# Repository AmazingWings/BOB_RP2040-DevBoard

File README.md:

<div align="center">

# BOB
### A Raspberry Pi RP2040 development board

### [Key Features](#key-features) • [PCB](#pcb) • [Credits](#credits) • [License](#license)

</div>

---

## Welcome!
Hi! This is my first SMT board! It is a custom RP2040 development board named BOB. I chose BOB as the name because I like Bob; it's a fun name to say. But on the other hand, it is designed to act as a platform for me to learn SMT board design. The reason why I made it was not only to learn how to make a fully SMT board, but to serve as a platform for learning for my future flight computer designs I will do for my rockets. I wanted to transition away from using software like EasyEDA to more professional software like KiCad, which is much more widely used. Through this project, I not only learned SMT schematic design but also routing. In EasyEDA, I used to autoroute my components, but in KiCad and through this project, I learned how to route components and place components by myself, transitioning away from my dependencies with breakout boards. 

### Key features:
1. Dual-core processor with up to 133 MHz in speed.
2. 264 KB of on-chip SRAM.
3. Programmable through USB-C.
4. 30 GPIO pins that can run I2C, SPI, and UART. 
5. 2-layer PCB design: top layer for components and bottom layer for ground wiring and signal routing, along with the top layer for signal wiring and power wiring.

---

## PCB

### Schematic Design 

### PCB Design

### 3D Design

### JLC PCB 3D Design

### BOM

### Final Cost Estimate

---

## Credits
1. https://macondo.hackclub.com/docs/build-a-devboard
2. [KiCad](https://www.kicad.org/) 
3. [JLCPCB](https://jlcpcb.com/)

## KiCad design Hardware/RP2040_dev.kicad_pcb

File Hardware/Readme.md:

<div align="center">

# Production Files
### RP2040 BOB Devboard
</div>

---

This folder contains all the necessary production files required to manufacture the **RP2040 BOB devboard**. 

---

## 🛠️ How to Use (Manufacturing)

If you want to order this board, simply **drag and drop the entire folder into JLCPCB**. Their system will automatically detect and compile all the necessary files you need for production.

## 📄 Key Files

* **BOM (Bill of Materials):** Provided in standard `.csv` format, ready for component sourcing and assembly.

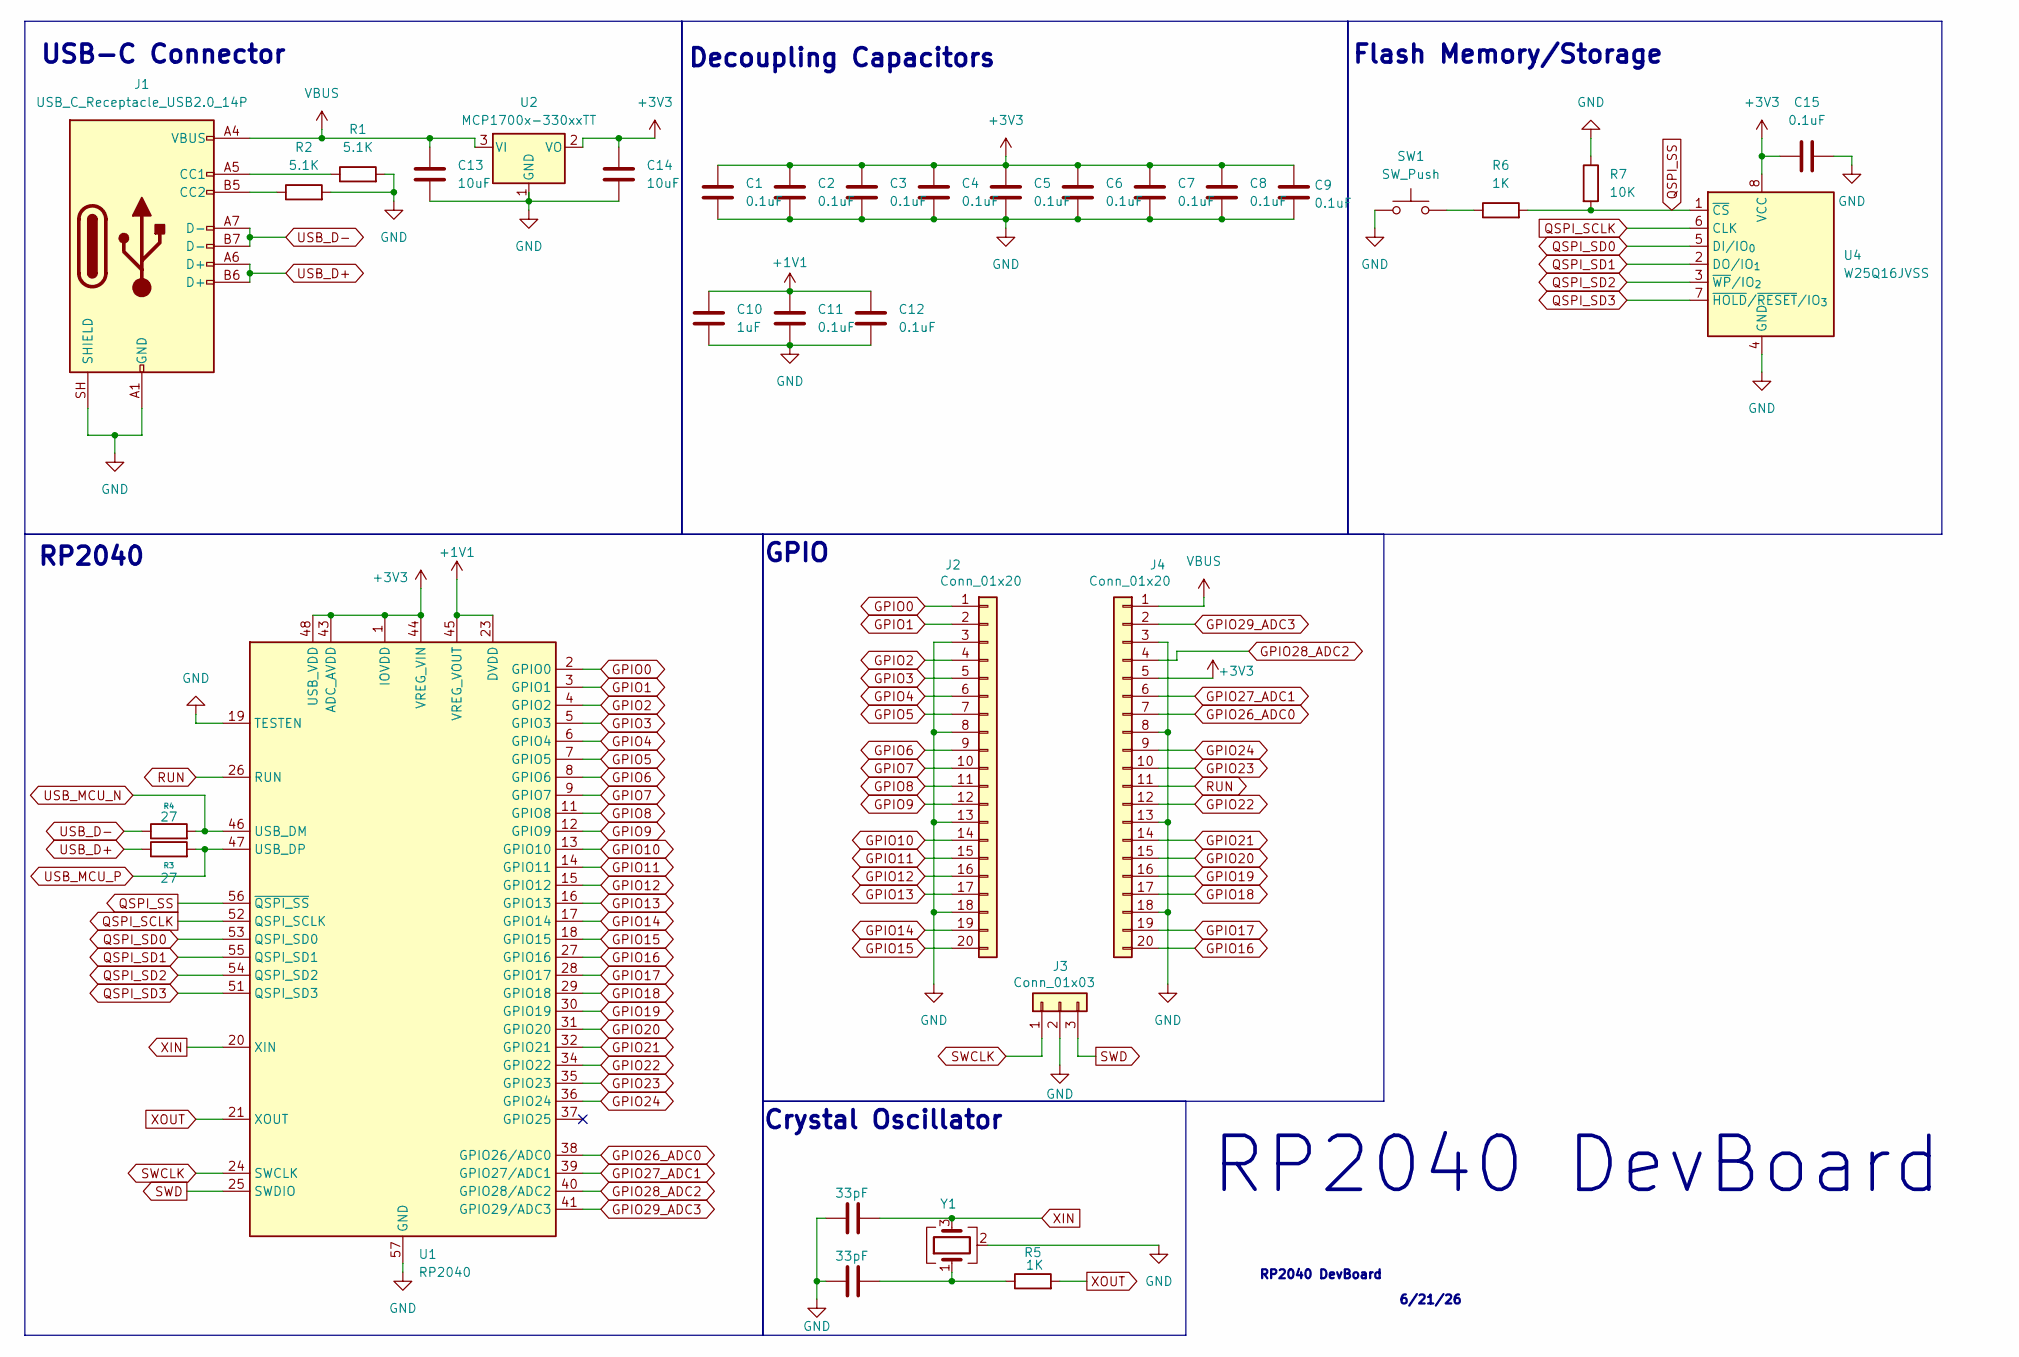
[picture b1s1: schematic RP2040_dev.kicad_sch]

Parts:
33pF2, 33pF3: 33pF; C_0402_1005Metric
C1, C2, C3, C4, C5, C6, C7, C8, C9, C11, C12, C15: 0.1uF; C_0402_1005Metric
C10: 1uF; C_0402_1005Metric
C13, C14: 10uF; C_0603_1608Metric
J1: USB_C_Receptacle_USB2.0_14P; USB_C_Receptacle_HRO_TYPE-C-31-M-12
J2, J4: Conn_01x20; PinHeader_1x20_P2.54mm_Vertical
J3: Conn_01x03; PinHeader_1x03_P2.54mm_Vertical
R1, R2: 5.1K; R_0402_1005Metric
R3, R4: 27; R_0402_1005Metric
R5, R6: 1K; R_0402_1005Metric
R7: 10K; R_0402_1005Metric
SW1: SW_Push; SW_Push_SPST_NO_Alps_SKRK
U1: RP2040; QFN-56-1EP_7x7mm_P0.4mm_EP3.2x3.2mm
U2: MCP1700x-330xxTT; SOT-23
U4: W25Q16JVSS; Winbond_USON-8-1EP_3x2mm_P0.5mm_EP0.2x1.6mm
Y1: 12mhz; Crystal_SMD_3225-4Pin_3.2x2.5mm

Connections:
+1V1: C10.1, C11.1, C12.1, U1.23 (DVDD), U1.45 (VREG_VOUT), U1.50 (DVDD)
+3V3: C1.1, C2.1, C3.1, C4.1, C5.1, C6.1, C7.1, C8.1, C9.1, C14.1, C15.1, J4.5, U1.1 (IOVDD), U1.10 (IOVDD), U1.22 (IOVDD), U1.33 (IOVDD), U1.42 (IOVDD), U1.43 (ADC_AVDD), U1.44 (VREG_VIN), U1.48 (USB_VDD), U1.49 (IOVDD), U2.2 (VO), U4.8 (VCC)
GND: 33pF2.1, 33pF3.1, C1.2, C2.2, C3.2, C4.2, C5.2, C6.2, C7.2, C8.2, C9.2, C10.2, C11.2, C12.2, C13.2, C14.2, C15.2, J1.A1 (GND), J1.A12 (GND), J1.B1 (GND), J1.B12 (GND), J1.SH (SHIELD), J2.3, J2.8, J2.13, J2.18, J3.2, J4.3, J4.8, J4.13, J4.18, R1.2, R2.2, R7.1, SW1.1, U1.19 (TESTEN), U1.57 (GND), U2.1 (GND), U4.4 (GND), Y1.2 (G), Y1.4 (G)
GPIO0: J2.1, U1.2 (GPIO0)
GPIO1: J2.2, U1.3 (GPIO1)
GPIO2: J2.4, U1.4 (GPIO2)
GPIO3: J2.5, U1.5 (GPIO3)
GPIO4: J2.6, U1.6 (GPIO4)
GPIO5: J2.7, U1.7 (GPIO5)
GPIO6: J2.9, U1.8 (GPIO6)
GPIO7: J2.10, U1.9 (GPIO7)
GPIO8: J2.11, U1.11 (GPIO8)
GPIO9: J2.12, U1.12 (GPIO9)
GPIO10: J2.14, U1.13 (GPIO10)
GPIO11: J2.15, U1.14 (GPIO11)
GPIO12: J2.16, U1.15 (GPIO12)
GPIO13: J2.17, U1.16 (GPIO13)
GPIO14: J2.19, U1.17 (GPIO14)
GPIO15: J2.20, U1.18 (GPIO15)
GPIO16: J4.20, U1.27 (GPIO16)
GPIO17: J4.19, U1.28 (GPIO17)
GPIO18: J4.17, U1.29 (GPIO18)
GPIO19: J4.16, U1.30 (GPIO19)
GPIO20: J4.15, U1.31 (GPIO20)
GPIO21: J4.14, U1.32 (GPIO21)
GPIO22: J4.12, U1.34 (GPIO22)
GPIO23: J4.10, U1.35 (GPIO23)
GPIO24: J4.9, U1.36 (GPIO24)
GPIO26_ADC0: J4.7, U1.38 (GPIO26/ADC0)
GPIO27_ADC1: J4.6, U1.39 (GPIO27/ADC1)
GPIO28_ADC2: J4.4, U1.40 (GPIO28/ADC2)
GPIO29_ADC3: J4.2, U1.41 (GPIO29/ADC3)
unnamed: 33pF2.2, R5.1, Y1.1
unnamed: J1.A5 (CC1), R1.1
unnamed: J1.B5 (CC2), R2.1
unnamed: R6.1, SW1.2
QSPI_SCLK: U1.52 (QSPI_SCLK), U4.6 (CLK)
QSPI_SD0: U1.53 (QSPI_SD0), U4.5 (DI/IO_{0})
QSPI_SD1: U1.55 (QSPI_SD1), U4.2 (DO/IO_{1})
QSPI_SD2: U1.54 (QSPI_SD2), U4.3 (~WP/IO_{2})
QSPI_SD3: U1.51 (QSPI_SD3), U4.7 (~HOLD/~RESET/IO_{3})
QSPI_SS: R6.2, R7.2, U1.56 (~QSPI_SS), U4.1 (~CS)
RUN: J4.11, U1.26 (RUN)
SWCLK: J3.1, U1.24 (SWCLK)
SWD: J3.3, U1.25 (SWDIO)
USB_D+: J1.A6 (D+), J1.B6 (D+), R3.1
USB_D-: J1.A7 (D-), J1.B7 (D-), R4.1
USB_MCU_N: R4.2, U1.46 (USB_DM)
USB_MCU_P: R3.2, U1.47 (USB_DP)
VBUS: C13.1, J1.A4 (VBUS), J1.A9 (VBUS), J1.B4 (VBUS), J1.B9 (VBUS), J4.1, U2.3 (VI)
XIN: 33pF3.2, U1.20 (XIN), Y1.3
XOUT: R5.2, U1.21 (XOUT)

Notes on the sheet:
RP2040
USB-C Connector
Flash Memory/Storage
Crystal Oscillator
GPIO
RP2040 DevBoard
Decoupling Capacitors
6/21/26

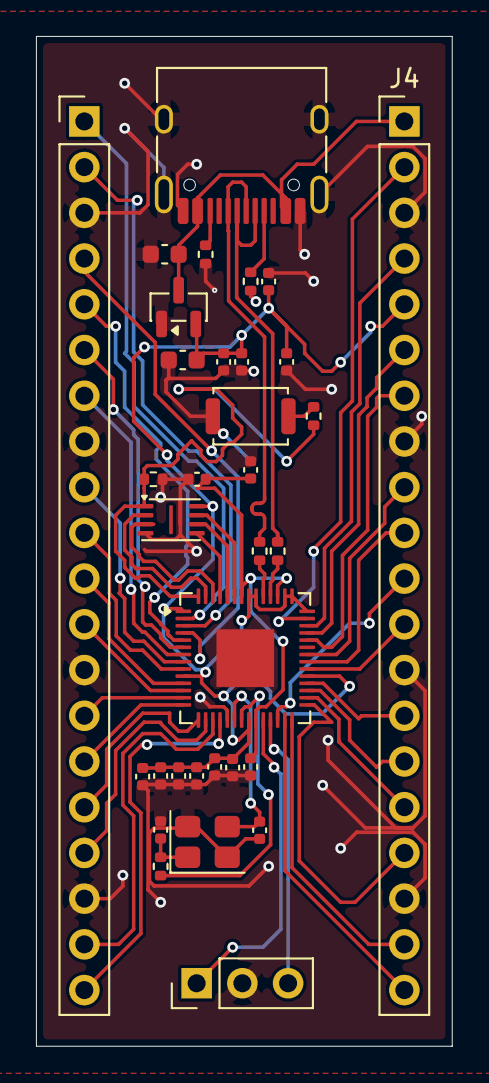
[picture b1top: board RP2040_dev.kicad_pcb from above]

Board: 2 copper layers, 23.1 x 56.1 mm, 33 parts (0 on the bottom side), 52 nets.

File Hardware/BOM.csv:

RP2040_dev
Id,Designator,Footprint,Quantity,Comment,Supplier and ref,,
1,"33pF2, 33pF3",C_0402_1005Metric,2,33pF,,,
2,"C1, C2, C3, C4, C5, C6, C7, C8, C9, C11, C12, C15",C_0402_1005Metric,12,0.1uF,,,
3,C10,C_0402_1005Metric,1,1uF,,,
4,"C13, C14",C_0603_1608Metric,2,10uF,,,
5,J1,USB_C_Receptacle_HRO_TYPE-C-31-M-12,1,USB_C_Receptacle_USB2.0_14P,,,
6,"J2, J4",PinHeader_1x20_P2.54mm_Vertical,2,Conn_01x20,,,
7,J3,PinHeader_1x03_P2.54mm_Vertical,1,Conn_01x03,,,
8,"R1, R2",R_0402_1005Metric,2,5.1K,,,
9,"R3, R4",R_0402_1005Metric,2,27,,,
10,"R5, R6",R_0402_1005Metric,2,1K,,,
11,R7,R_0402_1005Metric,1,10K,,,
12,SW1,SW_Push_SPST_NO_Alps_SKRK,1,SW_Push,,,
13,U1,QFN-56-1EP_7x7mm_P0.4mm_EP3.2x3.2mm,1,RP2040,,,
14,U2,SOT-23,1,MCP1700x-330xxTT,,,
15,U4,Winbond_USON-8-1EP_3x2mm_P0.5mm_EP0.2x1.6mm,1,W25Q16JVSS,,,
16,Y1,Crystal_SMD_3225-4Pin_3.2x2.5mm,1,12mhz,,,
